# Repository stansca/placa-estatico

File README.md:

# Placa do teste estático — UTFPR Rocket

Placa de aquisição para o **teste estático de motor**: mede o empuxo com uma célula de carga (HX711) e grava no cartão microSD. É usada pela propulsão nos estáticos dos foguetes de 500 m (F-500) e 1 km (MWTH). Feita pela aviônica, equipe Rocket 2026-1.

| | |
|---|---|
| PCB | 2 camadas, 26 componentes, 51 nets (KiCad 10) |
| Microcontrolador | ESP32-DevKitC-32E |
| Célula de carga | módulo HX711 (DT = GPIO21, SCK = GPIO22), alimentado em 5 V |
| Pressão | entrada analógica no IO34 (não há BMP280 nesta placa) |
| Armazenamento | adaptador microSD |
| Alimentação | conversor buck + bornes AK500 |
| Sinalização | buzzer (BC548) e LEDs |

## Abrir no KiCad
Usa componentes da biblioteca da equipe: [kicad-biblioteca-js](https://github.com/stansca/kicad-biblioteca-js). Instale-a e defina a variável `JS_KICAD_LIB` antes de abrir o projeto.

## Firmware
- Teste da célula de carga (tara, calibração com peso conhecido, ruído): `teste_celula_carga`, no repositório [rocket-arduino](https://github.com/stansca/rocket-arduino).
- Antes do teste estático, ligue o HX711 em **80 amostras/s** (pino RATE em nível alto). O padrão de 10/s dá só ~40 pontos numa queima de ~4 s.

## Pendências
- [ ] Confirmar se a placa foi fabricada.
- [ ] Calibrar a célula da equipe e anotar a escala aqui.

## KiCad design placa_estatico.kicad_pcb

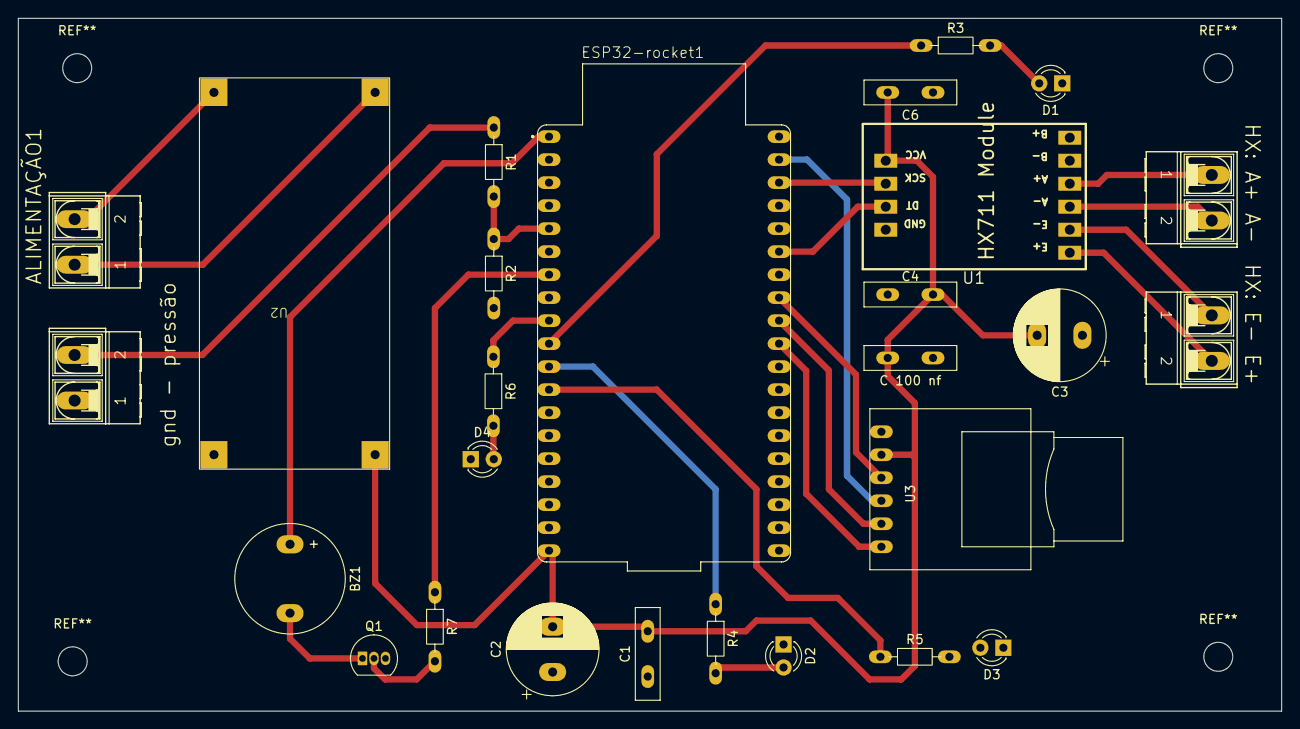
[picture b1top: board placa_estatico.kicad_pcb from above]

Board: 2 copper layers, 139.5 x 76.5 mm, 27 parts (0 on the bottom side), 28 nets.

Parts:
ALIMENTAÇÃO1: Screw_Terminal_01x02; Borne_AK500-2
BZ1: Buzzer; Buzzer_12x9.5RM7.6
C1, C4, C6: 100 nf; C_Disc_D10.0mm_W2.5mm_P5.00mm
C2, C3: 10 uf; CP_Radial_D10.0mm_P5.00mm
C 100 nf: 100 nf; C_Disc_D10.0mm_W2.5mm_P5.00mm
D1: LED-balança; LED_D3.0mm
D2: LED-pressão; LED_D3.0mm
D3: LED-SD; LED_D3.0mm
D4: LED-esp32; LED_D3.0mm
ESP32-rocket1: ESP32-DEVKITC-32E; ESP32-DevKitC-32E
HX: A+ A-: Screw_Terminal_01x02; Borne_AK500-2
HX: E- E+: Screw_Terminal_01x02; Borne_AK500-2
Q1: BC548; TO-92_Inline
R1, R3, R4, R5, R6: 10K; R_Axial_DIN0204_L3.6mm_D1.6mm_P7.62mm_Horizontal
R2: 20K; R_Axial_DIN0204_L3.6mm_D1.6mm_P7.62mm_Horizontal
R7: 1K; R_Axial_DIN0204_L3.6mm_D1.6mm_P7.62mm_Horizontal
U1: HX711_Modulo
U2: Buck_Conversor
U3: SD_Card_Adapter
gnd - pressão: Screw_Terminal_01x02; Borne_AK500-2

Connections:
/3v3: BZ1.1 (+), ESP32-rocket1.J2_1 (3V3)
/5v5: C1.2, C2.2, C3.2, C4.2, C6.2, C 100 nf.2, ESP32-rocket1.J2_19 (EXT_5V), U1.4 (Vcc), U2.2 (OUT+5), U3.2 (VCC)
/12+: ALIMENTAÇÃO1.1, U2.3 (IN+12)
/12-: ALIMENTAÇÃO1.2, U2.4 (IN-12)
/A+: HX: A+ A-.1, U1.7 (A+)
/A-: HX: A+ A-.2, U1.8 (A-)
/AzulPressão: R1.1, gnd - pressão.2
/BUZZER-gpio32: ESP32-rocket1.J2_7 (IO32), R7.1
/E+: HX: E- E+.2, U1.10 (E+)
/E-: HX: E- E+.1, U1.9 (E-)
/GND: C1.1, C2.1, C3.1, C4.1, C6.1, C 100 nf.1, D1.1 (K), D2.1 (K), D3.1 (K), D4.1 (K), ESP32-rocket1.J2_14 (GND_J2_14), ESP32-rocket1.J3_1 (GND_J3_1), ESP32-rocket1.J3_7 (GND_J3_7), Q1.3 (E), R2.2, U1.1 (Gnd), U2.1 (OUT-5), U3.1 (GND), gnd - pressão.1
/SaidaPressão: ESP32-rocket1.J2_5 (IO34), R1.2, R2.1
/gpio-05 cs sd: ESP32-rocket1.J3_10 (IO5), U3.6 (CS)
/gpio-14 led sd: ESP32-rocket1.J2_12 (IO14), R5.1
/gpio-18 sck sd: ESP32-rocket1.J3_9 (IO18), U3.5 (SCK)
/gpio-19 miso sd: ESP32-rocket1.J3_8 (IO19), U3.3 (MISO)
/gpio-21 dt HX: ESP32-rocket1.J3_6 (IO21), U1.2 (dt)
/gpio-22 sck HX: ESP32-rocket1.J3_3 (IO22), U1.3 (Sck)
/gpio-23 mosi sd: ESP32-rocket1.J3_2 (IO23), U3.4 (MOSI)
/gpio-25 led esp: ESP32-rocket1.J2_9 (IO25), R6.1
/gpio-26 led balanca: ESP32-rocket1.J2_10 (IO26), R3.1
/gpio-27 led pressao: ESP32-rocket1.J2_11 (IO27), R4.1
unnamed: BZ1.2 (-), Q1.1 (C)
unnamed: D1.2 (A), R3.2
unnamed: D2.2 (A), R4.2
unnamed: D3.2 (A), R5.2
unnamed: D4.2 (A), R6.2
unnamed: Q1.2 (B), R7.2
